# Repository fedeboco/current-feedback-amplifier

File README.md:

# Current Feedback Topology 40W Audio Amplifier

The current feedback topology gives this amplifier some independency between gain and bandwidth, resulting in an amplifier with relatively high power and high bandwidth (around 450 kHz at full power). Having a higher bandwidth than the traditional audio band (up to 20 kHz) produces a lower phase distortion in the audio band, consequently producing better sound.

##### Specifications achieved:
| Specification   | Measured  |
| -------------   | -----:    |
| Power (RMS)     | 40 W      |
| Power Bandwidth | 450 kHz   |
| Bandwidth       |    1MHz   |
| SNR             | 84 dB     |
| THD (40W)       | 0.2%      |
| THD (1W)        | 0.012%    |
| IMD (1W)        | -78 dB    |
| Gain            | 24.5 dB   |

## Design

Heatsink has been designed using FreeCad and circuit using KiCad.

## Schematic

## Total Harmonic Distortion Measured

Distortion did not exceed 0,2% at full power, rating at around 0,1% on average of frequencies.

## Different views and base

## Previous Version

This version was bigger than the current version. It was also difficult to measure, more unstable and produced higher temperatures.

## PCB

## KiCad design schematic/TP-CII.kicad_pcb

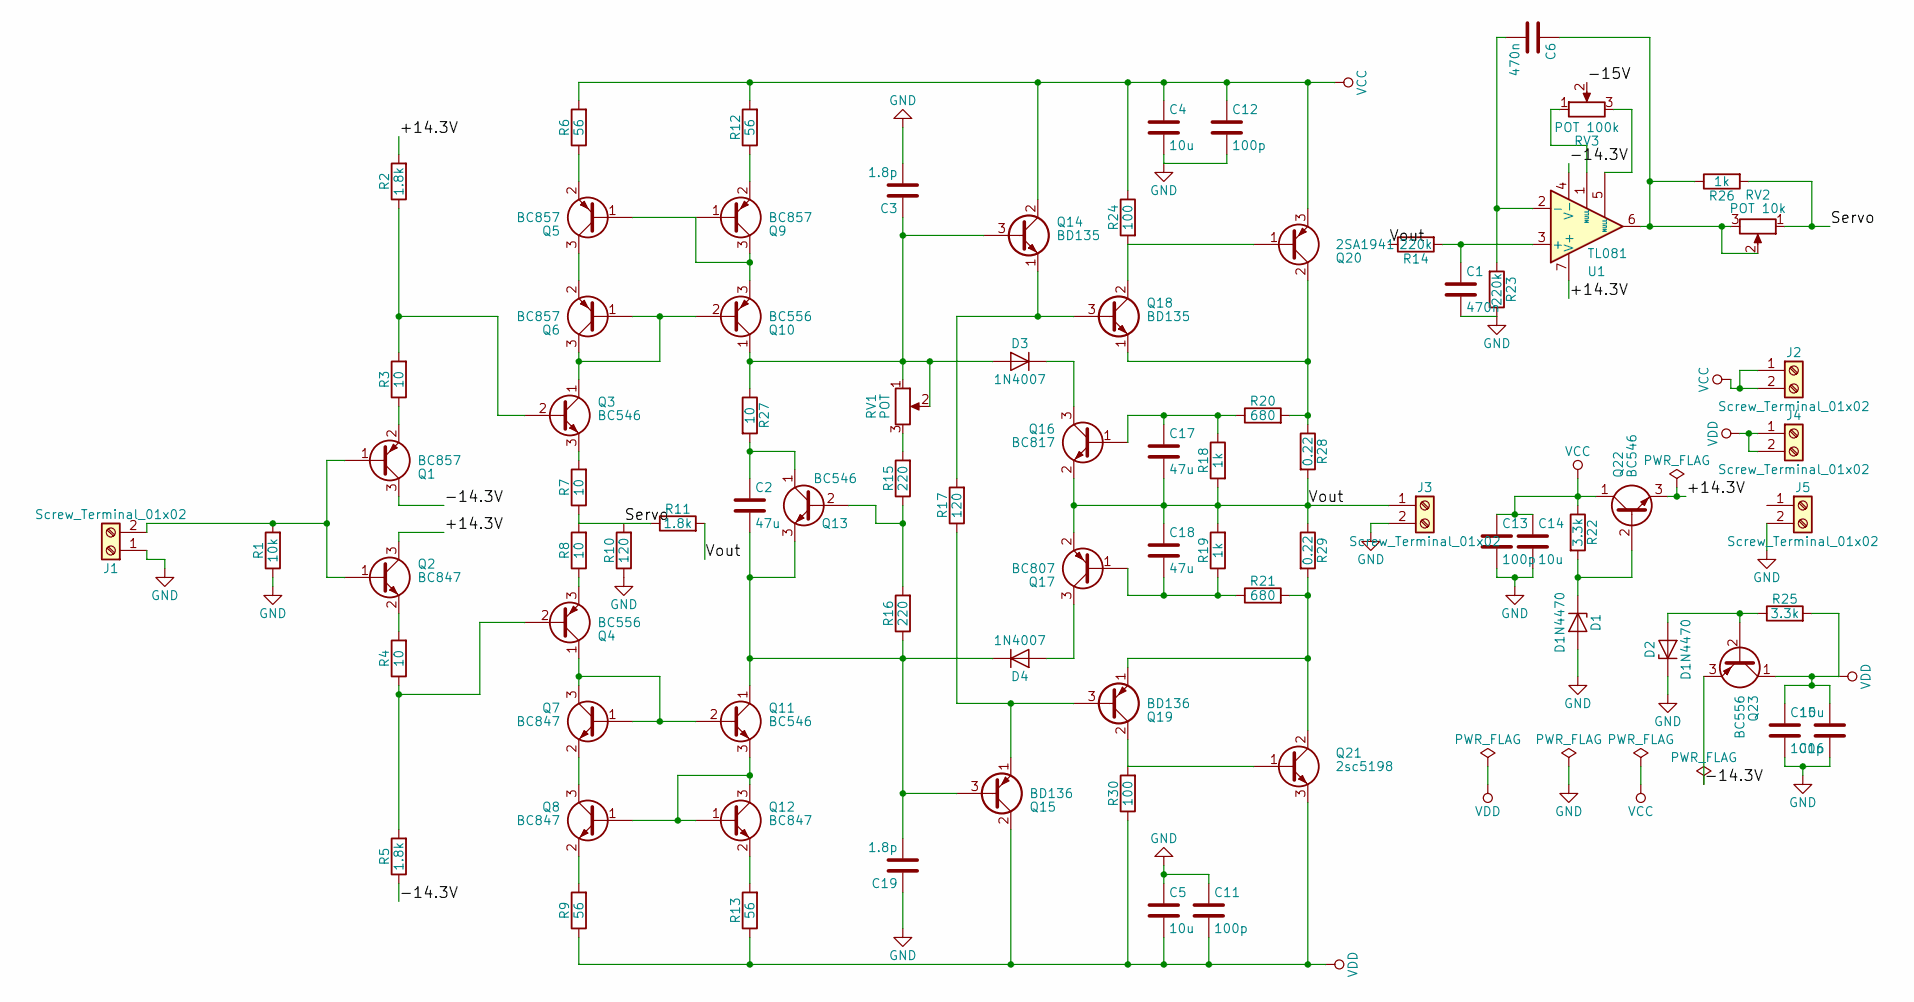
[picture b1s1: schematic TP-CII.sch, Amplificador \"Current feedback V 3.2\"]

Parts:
C1, C6: 470n; C_Rect_L9.0mm_W4.0mm_P7.50mm_MKT
C2: 47u; C_1206_3216Metric_Pad1.42x1.75mm_HandSolder
C3, C19: 1.8p; C_1206_3216Metric_Pad1.42x1.75mm_HandSolder
C4, C5, C14, C16: 10u; CP_Radial_D6.3mm_P2.50mm
C11, C12, C13, C15: 100p; C_1206_3216Metric_Pad1.42x1.75mm_HandSolder
C17, C18: 47u; CP_Elec_6.3x5.7
D1, D2: D1N4470; D_DO-35_SOD27_P7.62mm_Horizontal
D3, D4: 1N4007; D_DO-35_SOD27_P7.62mm_Horizontal
J1, J2, J3, J4, J5: Screw_Terminal_01x02; TerminalBlock_bornier-2_P5.08mm
Q1, Q5, Q6: BC857; TSOT-23_HandSoldering
Q2, Q7, Q8: BC847; TSOT-23_HandSoldering
Q3, Q11, Q13, Q22: BC546; TO-92
Q4, Q10, Q23: BC556; TO-92
Q9: BC857; SOT-23_Handsoldering
Q12: BC847; SOT-23_Handsoldering
Q14, Q18: BD135; TO-126_Vertical
Q15, Q19: BD136; TO-126_Vertical
Q16: BC817; TSOT-23_HandSoldering
Q17: BC807; TSOT-23_HandSoldering
Q20: 2SA1941; TO-3P-3_Vertical
Q21: 2sc5198; TO-3P-3_Vertical
R1: 10k; R_1206_3216Metric_Pad1.42x1.75mm_HandSolder
R2, R5, R11: 1.8k; R_1206_3216Metric_Pad1.42x1.75mm_HandSolder
R3, R4, R7, R8, R27: 10; R_1206_3216Metric_Pad1.42x1.75mm_HandSolder
R6, R9, R12, R13: 56; R_1206_3216Metric_Pad1.42x1.75mm_HandSolder
R10, R17: 120; R_1206_3216Metric_Pad1.42x1.75mm_HandSolder
R14, R23: 220k; R_1206_3216Metric_Pad1.42x1.75mm_HandSolder
R15, R16: 220; R_1206_3216Metric_Pad1.42x1.75mm_HandSolder
R18, R19, R26: 1k; R_1206_3216Metric_Pad1.42x1.75mm_HandSolder
R20, R21: 680; R_1206_3216Metric_Pad1.42x1.75mm_HandSolder
R22, R25: 3.3k; R_1206_3216Metric_Pad1.42x1.75mm_HandSolder
R24, R30: 100; R_1206_3216Metric_Pad1.42x1.75mm_HandSolder
R28, R29: 0.22; R_Axial_DIN0207_L6.3mm_D2.5mm_P10.16mm_Horizontal
RV1: POT; Potentiometer_Bourns_3266Y_Vertical
RV2: POT 10k; Potentiometer_Bourns_3266Y_Vertical
RV3: POT 100k; Potentiometer_Bourns_3266Y_Vertical
U1: TL081; DIP-8_W7.62mm_Socket

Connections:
/+15V: Q2.3 (C), Q22.3 (E), R2.2, U1.7 (V+)
/Servo: R7.1, R8.2, R10.2, R11.1, R26.2, RV2.1
/Vout: C17.2, C18.1, J3.1, Q16.2 (E), Q17.2 (E), R11.2, R14.1, R18.2, R19.2, R28.2, R29.1
GND: C1.2, C3.2, C4.2, C5.1, C11.1, C12.2, C13.2, C14.2, C15.2, C16.1, C19.1, D1.2 (A), D2.1 (K), J1.1, J3.2, J5.2, R1.1, R10.1, R23.1; also elsewhere on the board
unnamed: C1.1, R14.2, U1.3 (+)
unnamed: C2.1, Q13.1 (C), R27.2
unnamed: C3.1, D3.2 (A), Q10.1 (C), Q14.3 (B), R27.1, RV1.1, RV1.2
unnamed: C6.1, R26.1, RV2.2, RV2.3, U1.6
unnamed: C6.2, R23.2, U1.2 (-)
unnamed: C17.1, Q16.1 (B), R18.1, R20.1
unnamed: C18.2, Q17.1 (B), R19.1, R21.1
unnamed: C2.2, C19.2, D4.1 (K), Q11.1 (C), Q13.3 (E), Q15.3 (B), R16.1
unnamed: D1.1 (K), Q22.2 (B), R22.2
unnamed: D2.2 (A), Q23.2 (B), R25.1
unnamed: D3.1 (K), Q16.3 (C)
unnamed: D4.2 (A), Q17.3 (C)
unnamed: J1.2, Q1.1 (B), Q2.1 (B), R1.2
unnamed: Q1.2 (E), R3.1
unnamed: Q2.2 (E), R4.2
unnamed: Q3.2 (B), R2.1, R3.2
unnamed: Q3.3 (E), R7.2
unnamed: Q4.2 (B), R4.1, R5.2
unnamed: Q4.3 (E), R8.1
unnamed: Q5.2 (E), R6.1
unnamed: Q5.3 (C), Q6.2 (E)
unnamed: Q7.2 (E), Q8.3 (C)
unnamed: Q8.2 (E), R9.2
unnamed: Q9.2 (E), R12.1
unnamed: Q3.1 (C), Q6.1 (B), Q6.3 (C), Q10.2 (B)
unnamed: Q5.1 (B), Q9.1 (B), Q9.3 (C), Q10.3 (E)
unnamed: Q4.1 (C), Q7.1 (B), Q7.3 (C), Q11.2 (B)
unnamed: Q8.1 (B), Q11.3 (E), Q12.1 (B), Q12.3 (C)
unnamed: Q12.2 (E), R13.2
unnamed: Q13.2 (B), R15.1, R16.2
unnamed: Q14.1 (E), Q18.3 (B), R17.2
unnamed: Q15.1 (E), Q19.3 (B), R17.1
unnamed: Q18.1 (E), Q20.2 (C), R20.2, R28.1
unnamed: Q18.2 (C), Q20.1 (B), R24.2
unnamed: Q19.1 (E), Q21.2 (C), R21.2, R29.2
unnamed: Q19.2 (C), Q21.1 (B), R30.2
unnamed: R15.2, RV1.3
unnamed: RV3.1, U1.1 (NULL)
unnamed: RV3.3, U1.5 (NULL)
VCC: C4.1, C12.1, C13.1, C14.1, J2.1, J2.2, Q14.2 (C), Q20.3 (E), Q22.1 (C), R6.2, R12.2, R22.1, R24.1; also elsewhere on the board
VDD: C5.2, C11.2, C15.1, C16.2, J4.1, J4.2, Q15.2 (C), Q21.3 (E), Q23.1 (C), R9.1, R13.1, R25.2, R30.1

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
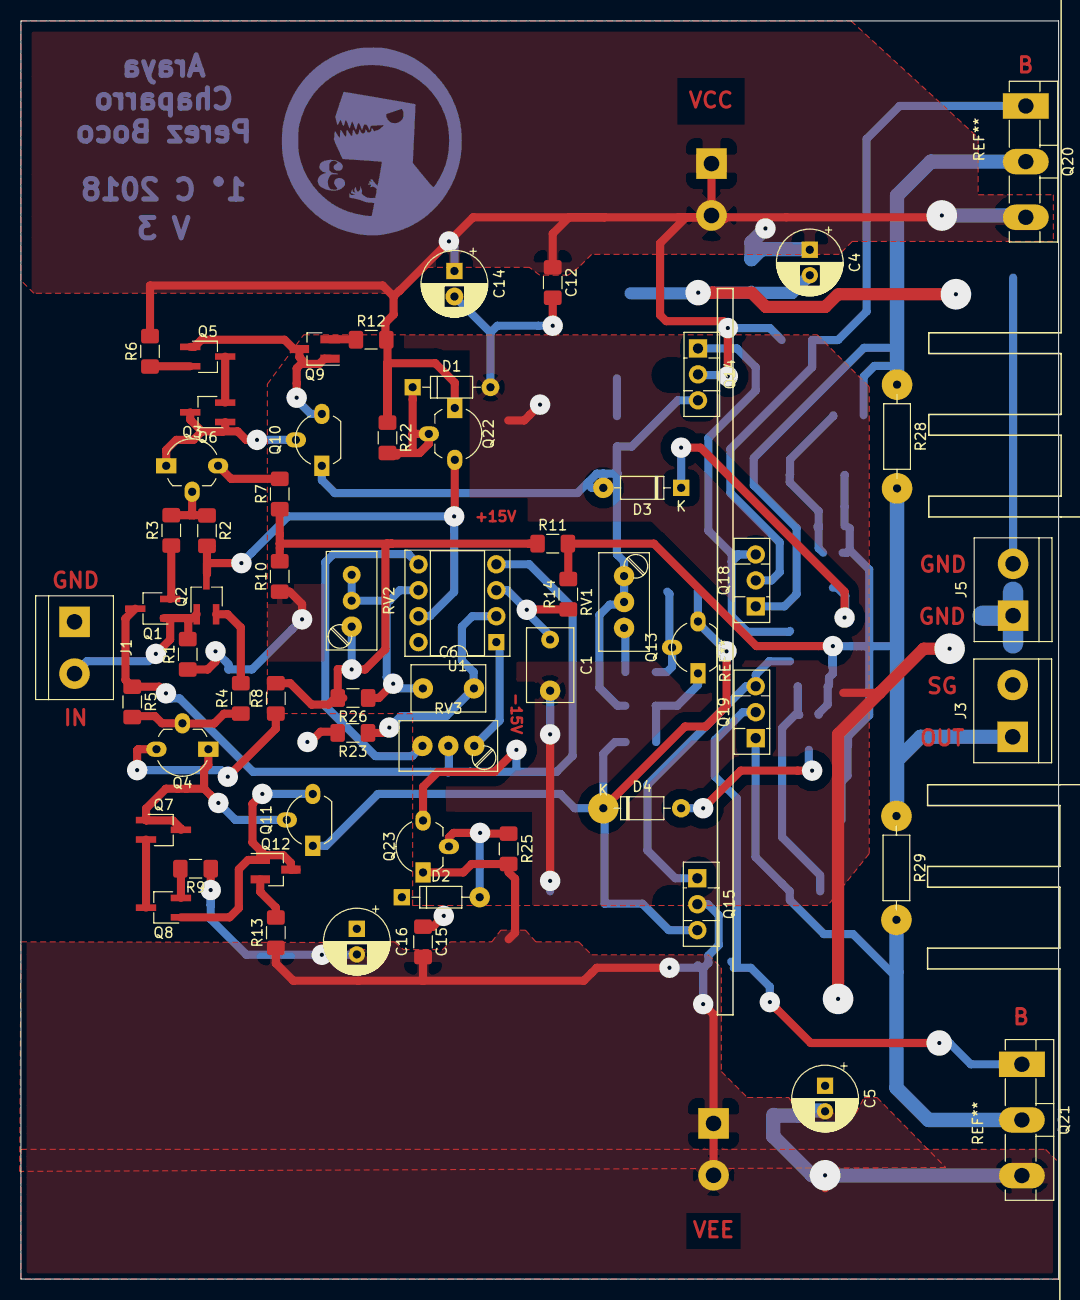
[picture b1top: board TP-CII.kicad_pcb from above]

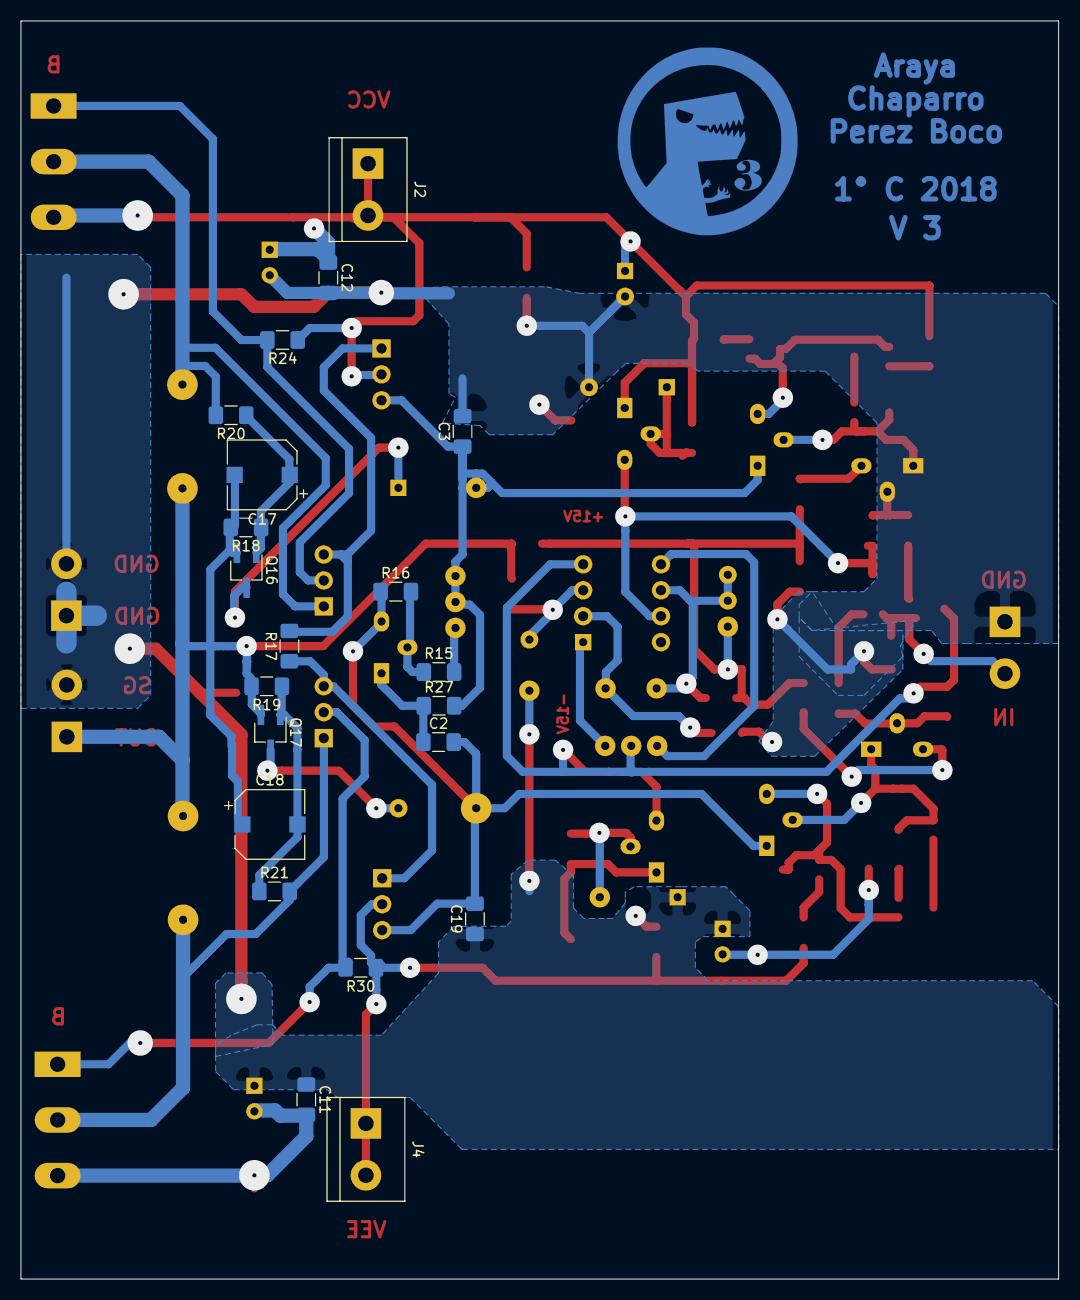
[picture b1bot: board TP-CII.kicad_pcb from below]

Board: 2 copper layers, 101.6 x 123.2 mm, 81 parts (21 on the bottom side), 46 nets.

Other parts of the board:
C12#2: 100p; C_1206_3216Metric_Pad1.42x1.75mm_HandSolder

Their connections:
GND: C12#2.2; also elsewhere on the board
VCC: C12#2.1; also elsewhere on the board
